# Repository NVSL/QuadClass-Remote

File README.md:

# CSE176e Quad Remote

## Assembly

## Parts

All the parts are on the course unified BOM: https://docs.google.com/spreadsheets/d/1jt7lCU-Biuc4YyG8EaISPEg1VLbqKCh2ZZRz8jerXEI/edit?gid=0#gid=0

## Laser Cutting

The plywood base and the "donuts" used for standoffs are all in the
`.brd` file.  Open it, hide everything but the `baseplate` layer.
Print it to a PDF and feed it to your laser cutter.

The wooden parts are cut from 3mm plywood (see parts list).

## The Gimbals

The gimbals attach to the baseplate with the 8 long machine screws and 8 nuts.  

## Board

The control board mounts to the baseplate using the shorter screws and nuts.  Use 3 donuts to put space between the board and the baseplate.

## Battery Cable

Red is positive.

Attach the battery and tuck it under the board.  You can trim the battery cable, if you want.  Experiment with different lengths.

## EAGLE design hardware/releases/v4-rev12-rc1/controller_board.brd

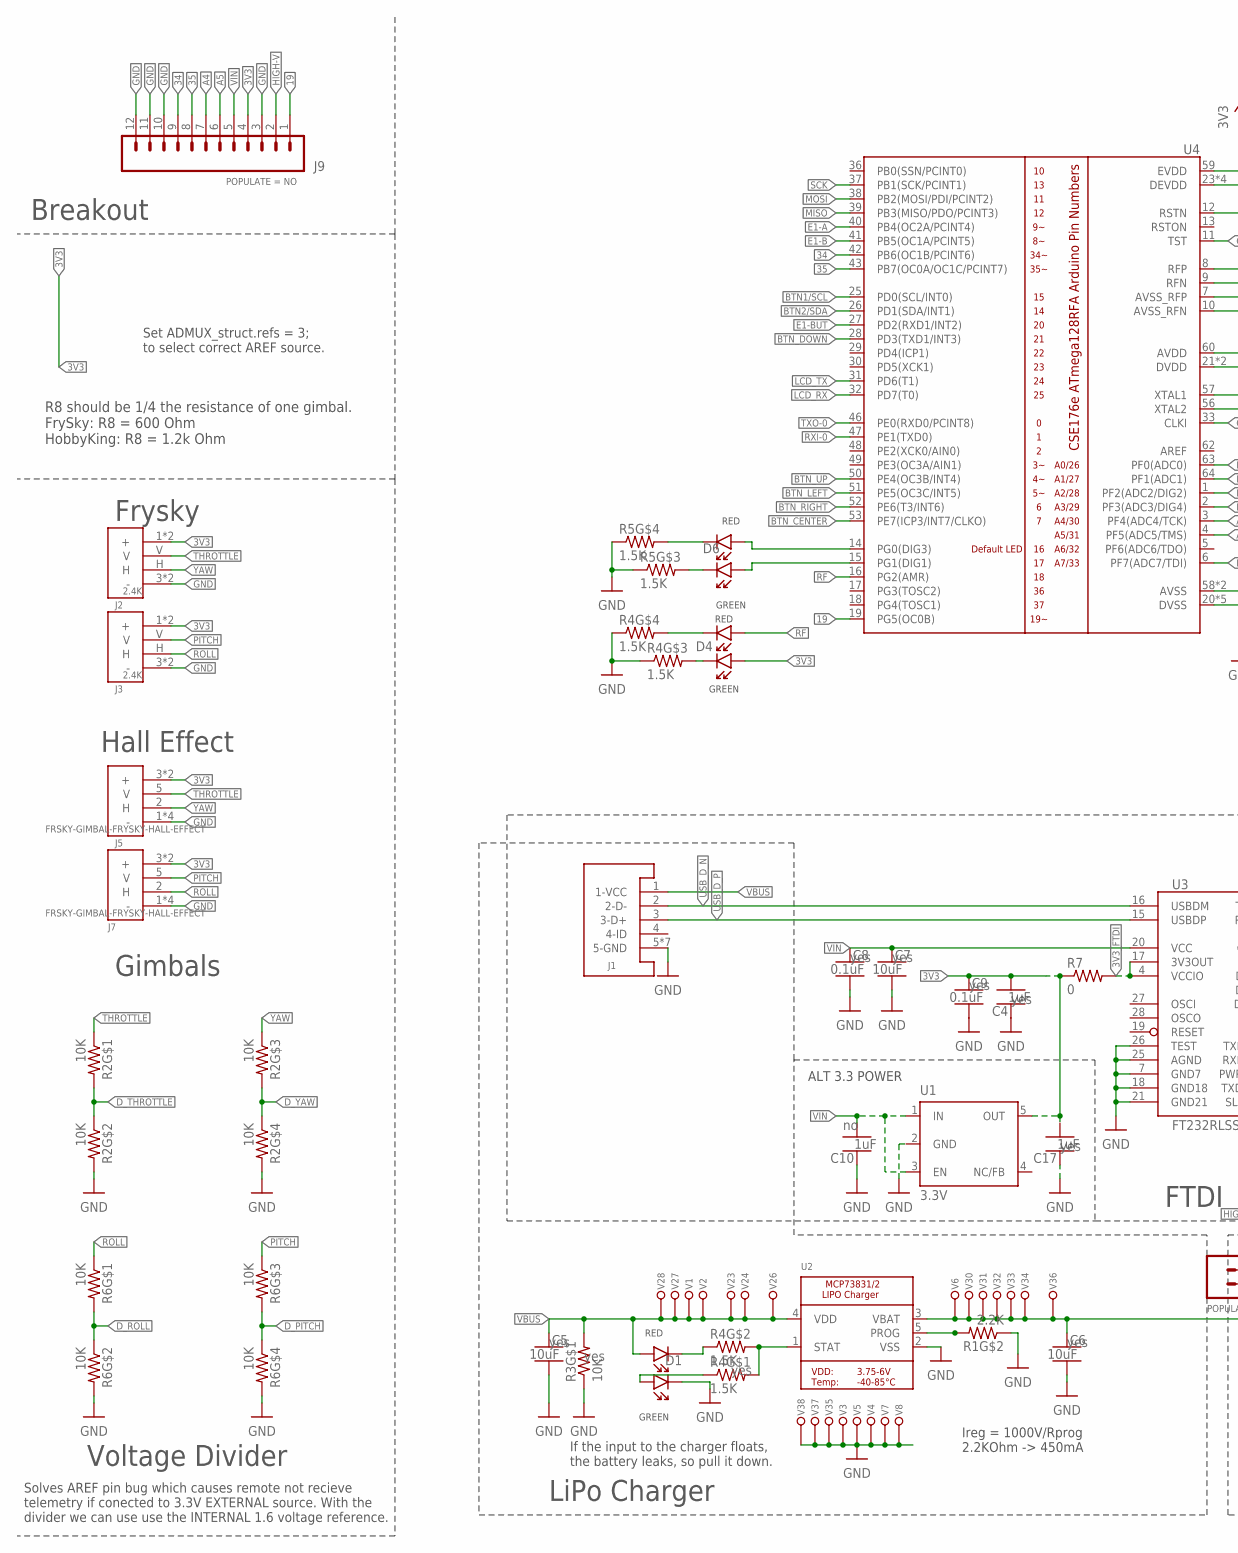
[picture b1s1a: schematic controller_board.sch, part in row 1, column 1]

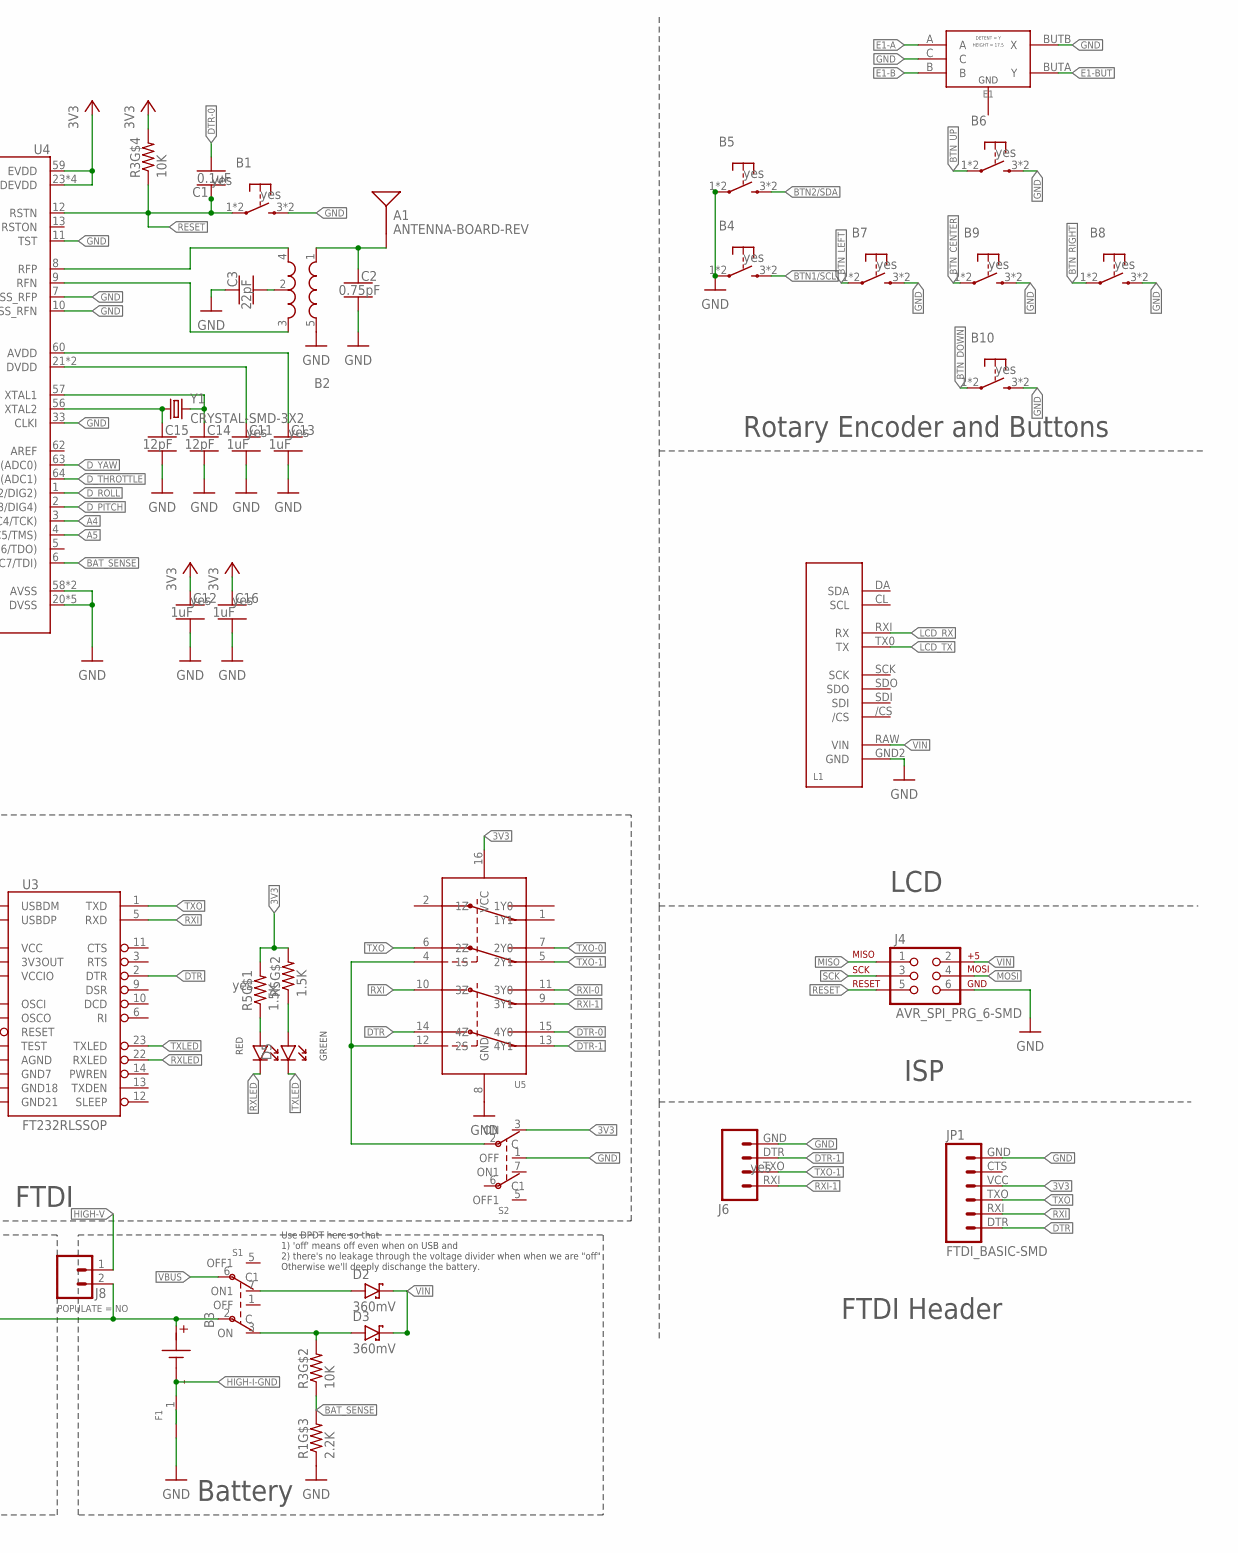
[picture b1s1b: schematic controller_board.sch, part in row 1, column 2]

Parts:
A1: ANTENNA-BOARD-REV; ANT_PCB_2.4GHZ_NRF8001_1.6MM_1OZ_REV
B1, B4, B5, B6, B7, B8, B9, B10: PUSHBUTTON_-4.5X4.5; 4.5MM_TACTILE_SWITCH_TL3305AF160QG
B2: BALUN0805; BALUN
B3: BATTERY-SCREW-TERMINAL; SCREW-TERMINAL-1X2-2.54MM
C1, C8, C9: 0.1uF; CAPC1608X100
C2: 0.75pF; CAPC1608X100
C3: 22pF; CAPC1608X100
C4, C10, C11, C12, C13, C16, C17: 1uF; CAPC1608X100
C5, C6, C7: 10uF; CAPC1608X100
C14, C15: 12pF; CAPC1608X100
D1, D4, D5, D6: LED-2X-GREEN/RED-1.6X1.5MM; LED-2X-LITE-ON-1.6MMX1.5MM
D2, D3: 360mV; SODFL3516X96
E1: ROTARY-ENCODER-W/BUTTON-BOURNS-PEC12R-4217F; BOURNS-PEC12R
F1: SHORT
J1: USB-MICROA-AMPHENOL-10118192-0001LF; USB-MICROA-10118192-0001LF
J2, J3: 2.4K; JST-13-PTH
J4: AVR_SPI_PRG_6-SMD; 2X3-SMD
J5, J7: FRSKY-GIMBAL-FRYSKY-HALL-EFFECT; MOLEX-0532610671
J6: FTDI-4PIN-RIGHT-ANGLE-SMD; HEADER-2X2-0.1IN-MALE-RIGHT-ANGLE-SMD
J8: HEADER-0.1IN-2POS-SCREW; SCREW-TERMINAL-1X2-2.54MM
J9: HEADER-12POS-0.1IN-FEMALE-TH; HDRVR12W75P254_1X12_3098X254X850B
JP1: FTDI_BASIC-SMD; FTDI-BASIC-SMD
L1: SPARKFUN_SERLCD_SERIAL_REDUCED-SMD; SPARKFUN_SERLCD_16X2_REDUCED_SMD
R1: 2.2K; RESCAXS50P200X100X45-8
R2, R3, R6: 10K; RESCAXS50P200X100X45-8
R4, R5: 1.5K; RESCAXS50P200X100X45-8
R7: 0; RESC1608X55
S1, S2: SWITCH-DPDT-300MA-6V-SMD; JS202011JCQN
U1: 3.3V; SOT23-DBV
U2: MCP73831T-2ACI/OT; SOT23-5
U3: FT232RLSSOP; SSOP28DB
U4: ATMEGA128RFA1; QFN-64
U5: DPDT-X2; SOP65P640X110-16
V1, V2, V3, V4, V5, V6, V7, V8, V23, V24, V26, V27, V28, V30, V31, V32, V33, V34, V35, V36, V37, V38: LOCKED-VIA-0.2; VIA-0.2MM
Y1: CRYSTAL-SMD-3X2; OSCCC320X250X85

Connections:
3V3: C4.2, C9.1, C12.1, C16.1, C17.2, D4.A1, J2.1 (+), J2.4 (+), J3.1 (+), J3.4 (+), J5.3 (+), J5.6 (+), J7.3 (+), J7.6 (+), J9.4, JP1.VCC (4), R3.8 (2), R5.5 (2), R5.6 (2), R7.1, S2.3 (ON), U1.5 (OUT), U4.23 (DEVDD), U4.34 (DEVDD), U4.44 (DEVDD), U4.54 (DEVDD), U4.59 (EVDD), U5.16 (VCC)
3V3_FTDI: R7.2, U3.4 (VCCIO), U3.17 (3V3OUT)
19: J9.1, U4.19 (PG5(OC0B))
34: J9.9, U4.42 (PB6(OC1B/PCINT6))
35: J9.8, U4.43 (PB7(OC0A/OC1C/PCINT7))
A4: J9.7, U4.3 (PF4(ADC4/TCK))
A5: J9.6, U4.4 (PF5(ADC5/TMS))
ANTENNA: A1.FEED, B2.1 (IN), C2.1
BAT_SENSE: R1.7 (2), R3.3 (1), U4.6 (PF7(ADC7/TDI))
BCAP: B2.2 (GND), C3.2
BPOS: B3.2, C6.1, J8.2 (1), S1.2 (C), U2.3 (VBAT), V6.P1, V30.P1, V31.P1, V32.P1, V33.P1, V34.P1, V36.P1
BTN1/SCL: B4.3 (2), B4.4 (2), U4.25 (PD0(SCL/INT0))
BTN2/SDA: B5.3 (2), B5.4 (2), U4.26 (PD1(SDA/INT1))
BTN_CENTER: B9.1, B9.2 (1), U4.53 (PE7(ICP3/INT7/CLKO))
BTN_DOWN: B10.1, B10.2 (1), U4.28 (PD3(TXD1/INT3))
BTN_LEFT: B7.1, B7.2 (1), U4.51 (PE5(OC3C/INT5))
BTN_RIGHT: B8.1, B8.2 (1), U4.52 (PE6(T3/INT6))
BTN_UP: B6.1, B6.2 (1), U4.50 (PE4(OC3B/INT4))
CLK_NEG: C15.1, U4.56 (XTAL2), Y1.1
CLK_POS: C14.1, U4.57 (XTAL1), Y1.3 (2)
DTR: JP1.DTR (1), U3.2 (DTR), U5.14 (4Z)
DTR-0: C1.2, U5.15 (4Y0)
DTR-1: J6.DTR (3), U5.13 (4Y1)
D_PITCH: R6.1, R6.7 (2), U4.2 (PF3(ADC3/DIG4))
D_ROLL: R6.3 (1), R6.5 (2), U4.1 (PF2(ADC2/DIG2))
D_THROTTLE: R2.3 (1), R2.5 (2), U4.64 (PF1(ADC1))
D_YAW: R2.1, R2.7 (2), U4.63 (PF0(ADC0))
E1-A: E1.A, U4.40 (PB4(OC2A/PCINT4))
E1-B: E1.B, U4.41 (PB5(OC1A/PCINT5))
E1-BUT: E1.BUTA (Y), U4.27 (PD2(RXD1/INT2))
GND: B1.3 (2), B1.4 (2), B2.5 (GND), B4.1, B4.2 (1), B5.1, B5.2 (1), B6.3 (2), B6.4 (2), B7.3 (2), B7.4 (2), B8.3 (2), B8.4 (2), B9.3 (2), B9.4 (2), B10.3 (2), B10.4 (2), C2.2, C3.1, C4.1, C5.2, C6.2, C7.2, C8.2, C9.2, C10.1, C11.2, C12.2, C13.2, C14.2, C15.2, C16.2, C17.1, D1.C1, E1.BUTB (X), E1.C, F1.2 (B), J1.5 (5-GND), J1.6 (5-GND), J1.7 (5-GND), J1.8 (5-GND), J1.9 (5-GND), J1.10 (5-GND), J1.11 (5-GND), J2.3 (-), J2.6 (-), J3.3 (-), J3.6 (-), J4.6, J5.1 (-), J5.4 (-), J5.G1 (-), J5.G2 (-), J6.GND (4), J7.1 (-), J7.4 (-), J7.G1 (-), J7.G2 (-), J9.3, J9.10, J9.11, J9.12, JP1.GND (6), L1.GND2 (GND), R1.2 (1), R1.3 (1), R2.6 (2), R2.8 (2), R3.4 (1), R4.1, R4.2 (1), R5.1, R5.2 (1), R6.6 (2), R6.8 (2), S2.1 (OFF), U1.2 (GND), U2.2 (VSS), U3.7 (GND7), U3.18 (GND18), U3.21 (GND21), U3.25 (AGND), U3.26 (TEST), U4.7 (AVSS_RFP), U4.10 (AVSS_RFN), U4.11 (TST), U4.20 (DVSS), U4.24 (DVSS), U4.33 (CLKI), U4.35 (DVSS), U4.45 (DVSS), U4.55 (DVSS), U4.58 (AVSS), U4.61 (AVSS), U5.8 (GND), V3.P1, V4.P1, V5.P1, V7.P1, V8.P1, V35.P1, V37.P1, V38.P1
HIGH-I-GND: B3.1 (N), F1.1 (A)
HIGH-V: J8.1 (2), J9.2
LCD_RX: L1.RXI (RX), U4.32 (PD7(T0))
LCD_TX: L1.TX0 (TX), U4.31 (PD6(T1))
MISO: J4.1, U4.39 (PB3(MISO/PDO/PCINT3))
MOSI: J4.4, U4.38 (PB2(MOSI/PDI/PCINT2))
unnamed: D1.A1, R4.4 (1)
unnamed: D1.C2, R4.3 (1)
unnamed: D5.A1, R5.3 (1)
unnamed: D6.C2, R5.8 (2)
unnamed: D6.C1, R5.7 (2)
unnamed: D4.C1, R4.7 (2)
unnamed: D5.A2, R5.4 (1)
unnamed: D6.A2, U4.14 (PG0(DIG3))
unnamed: D6.A1, U4.15 (PG1(DIG1))
unnamed: R4.5 (2), R4.6 (2), U2.1 (STAT)
unnamed: R1.6 (2), U2.5 (PROG)
unnamed: D4.C2, R4.8 (2)
unnamed: D2.2 (A), S1.7 (ON1)
unnamed: C11.1, U4.21 (DVDD), U4.22 (DVDD)
unnamed: C13.1, U4.60 (AVDD)
PITCH: J3.V, J7.5 (V), R6.2 (1)
PROG_SEL: S2.2 (C), U5.4 (1S), U5.12 (2S)
RESET: B1.1, B1.2 (1), C1.1, J4.5, R3.1, U4.12 (RSTN)
RF: D4.A2, U4.16 (PG2(AMR))
RF_N: B2.3 (OUT2), U4.9 (RFN)
RF_P: B2.4 (OUT1), U4.8 (RFP)
ROLL: J3.H, J7.2 (H), R6.4 (1)
RXI: JP1.RXI (2), U3.5 (RXD), U5.10 (3Z)
RXI-0: U4.47 (PE1(TXD0)), U5.11 (3Y0)
RXI-1: J6.RXI (1), U5.9 (3Y1)
RXLED: D5.C2, U3.22 (RXLED)
SCK: J4.3, U4.37 (PB1(SCK/PCINT1))
THROTTLE: J2.V, J5.5 (V), R2.4 (1)
TXLED: D5.C1, U3.23 (TXLED)
TXO: JP1.TXO (3), U3.1 (TXD), U5.6 (2Z)
TXO-0: U4.46 (PE0(RXD0/PCINT8)), U5.7 (2Y0)
TXO-1: J6.TXO (2), U5.5 (2Y1)
USB_D_N: J1.2 (2-D-), U3.16 (USBDM)
USB_D_P: J1.3 (3-D+), U3.15 (USBDP)
VBAT: D3.2 (A), R3.6 (2), S1.3 (ON)
VBUS: C5.1, D1.A2, J1.1 (1-VCC), R3.5 (2), S1.6 (C1), U2.4 (VDD), V1.P1, V2.P1, V23.P1, V24.P1, V26.P1, V27.P1, V28.P1
VIN: C7.1, C8.1, C10.2, D2.1 (C), D3.1 (C), J4.2, J9.5, L1.RAW (VIN), U1.1 (IN), U1.3 (EN), U3.20 (VCC)
YAW: J2.H, J5.2 (H), R2.2 (1)

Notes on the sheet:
Ireg = 1000V/Rprog 2.2KOhm -> 450mA
LiPo Charger
Breakout
Frysky
Hall Effect
Rotary Encoder and Buttons
Battery
LCD
ISP
FTDI Header
Set ADMUX_struct.refs = 3; to select correct AREF source.
Gimbals
R8 should be 1/4 the resistance of one gimbal. FrySky: R8 = 600 Ohm HobbyKing: R8 = 1.2k Ohm
If the input to the charger floats, the battery leaks, so pull it down.
FTDI
Use DPDT here so that 1) 'off' means off even when on USB and 2) there's no leakage through the voltage divider when when we are "off" Otherwise we'll deeply dischange the battery.
Voltage Divider
Solves AREF pin bug which causes remote not recieve telemetry if conected to 3.3V EXTERNAL source. With the divider we can use use the INTERNAL 1.6 voltage reference.
ALT 3.3 POWER

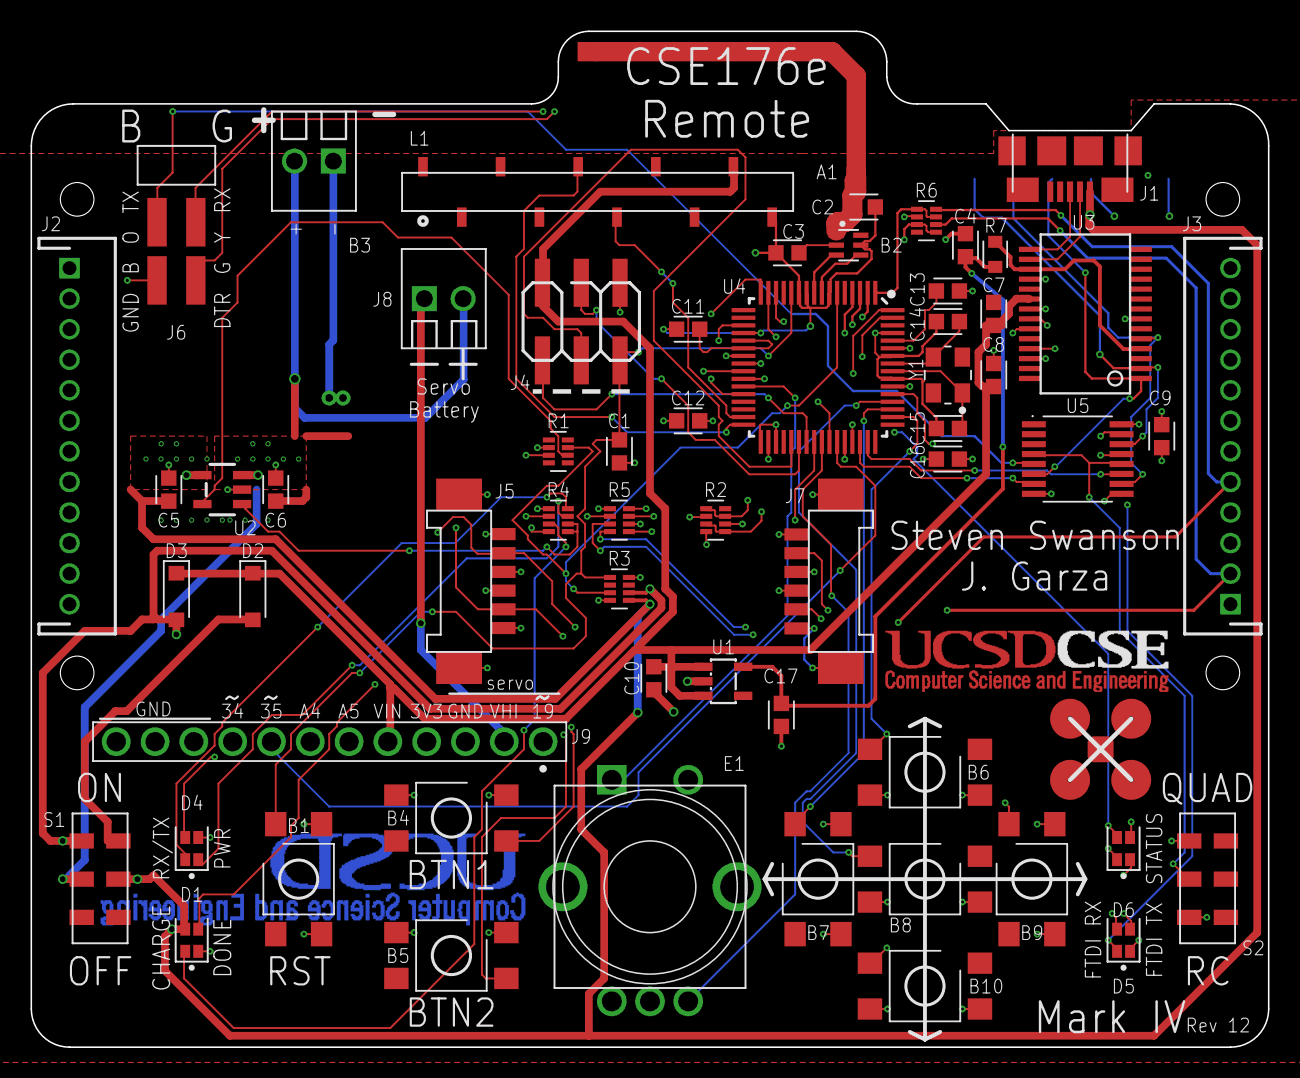
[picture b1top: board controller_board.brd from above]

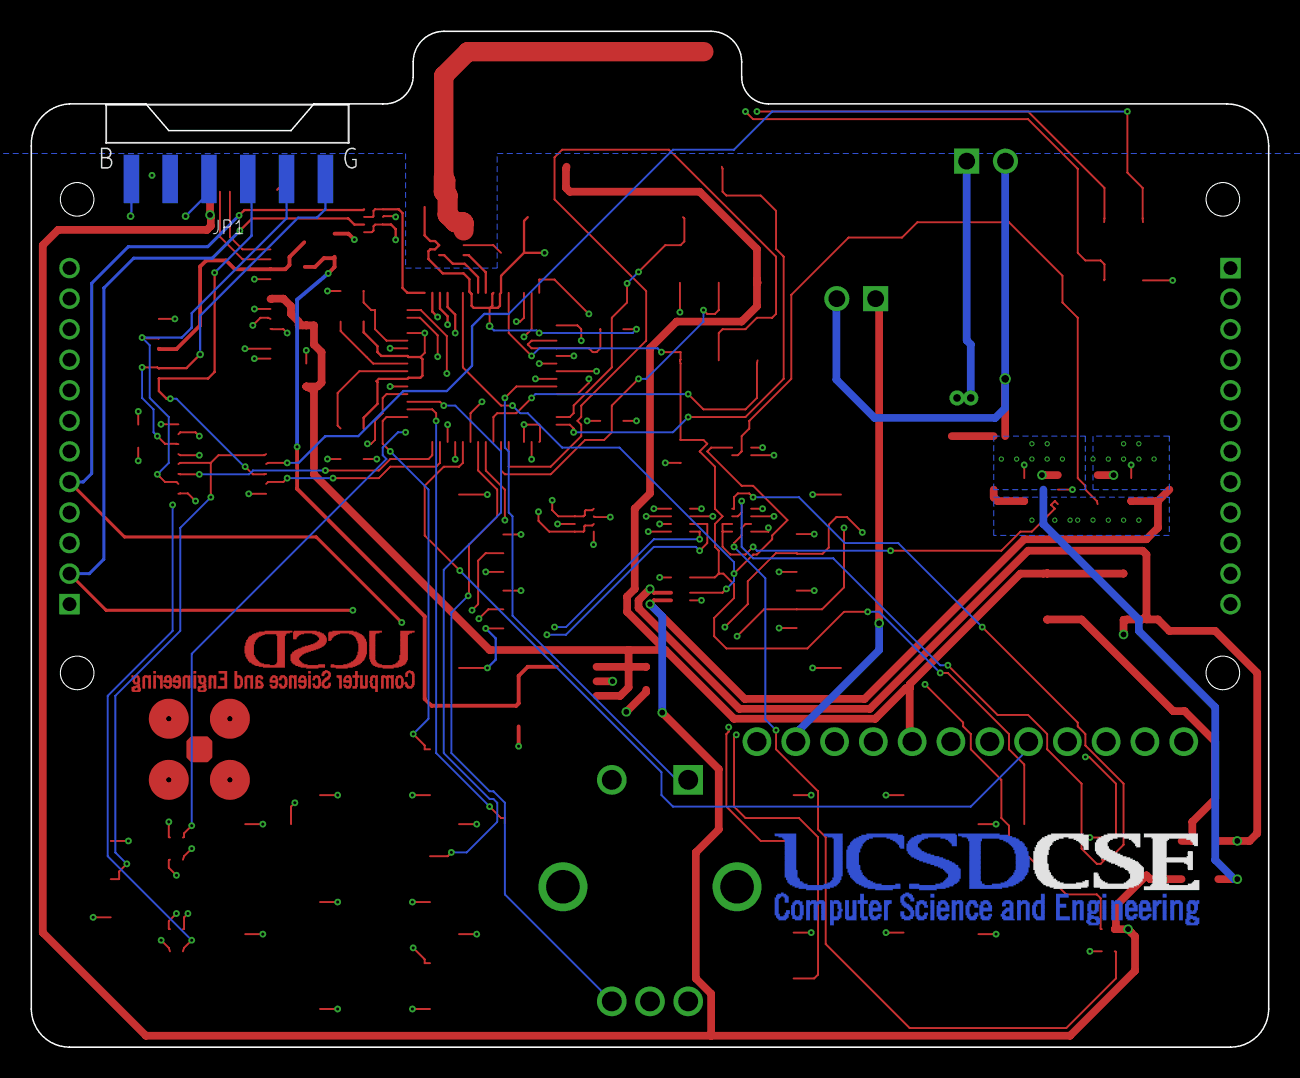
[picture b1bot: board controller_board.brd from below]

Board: 4 copper layers, 81.0 x 66.5 mm, 93 parts (2 on the bottom side), 75 nets.

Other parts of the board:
E$1, E$2: FRSKY-TARANIS-GIMBAL
U$1: 700MAH-BATTERY
U$2: QUADCLASS_LOGO_SMALL
U$3: LAYER_LABELS
U$4: 375MAH-BATTERY
U$5: 600MAH-BATTERY
U$6, U$7: CSE

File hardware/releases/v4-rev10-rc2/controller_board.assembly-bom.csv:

mfr,mfrpn,dist,distpn,part_list,qty,desc,value,substitute_ok,case,mounting,layer,pins,extended_pins,comments
C&K,JS202011JCQN,DIGIKEY,CKN10723CT-ND,S2 S1,2,SWITCH SLIDE DPDT 300MA 6V,SWITCH-DPDT-300MA-6V-SMD,no,,SMD,top,6,12,
Microchip Technology,ATMEGA128RFA1-ZU,DIGIKEY,ATMEGA128RFA1-ZU-ND ,U4,1,IC RF TXRX+MCU 802.15.4 64VFQFN,ATMEGA128RFA1,no,QFN,SMD,top,64,64,
Samsung Electro-Mechanics,CL10A105KP8NNNC,DIGIKEY,1276-1182-1-ND,C4 C13 C12 C11 C16,5,CAP CER 1UF 10V X5R 0603,1uF,yes,0603,SMD,top,2,10,
Abracon LLC,ABM8-16.000MHZ-B2-T,DIGIKEY,535-9134-1-ND,Y1,1,CRYSTAL 16.0000MHZ 18PF SMD,CRYSTAL-SMD-3X2,no,,SMD,top,4,4,
UNKNOWN,UNKNOWN,ALIBABA,https://www.alibaba.com/product-detail/Molex-51005-51006-2-p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,B3,1,Surface mount  battery connector,BATTERY-SMD,no,,SMD,top,4,4,
Sullins Connector Solutions,NPPC101KFXC-RC,DIGIKEY,S5641-ND,L1,1,"10 Position Header, Top or Bottom Entry Connector  Surface Mount",SPARKFUN_SERLCD_SERIAL_REDUCED-SMD,no,,SMD,top,10,10,
Toshiba Semiconductor and Storage,"CRS08(TE85L,Q,M)",DIGIKEY,CRS08QMCT-ND,D2 D3,2,DIODE SCHOTTKY 30V 1.5A SFLAT,360mV,no,,SMD,top,2,4,
Yageo,CC0603BRNPO9BNR75,DIGIKEY,311-3843-1-ND,C2,1,CAP CER 0.75PF 50V NPO 0603,0.75pF,no,0603,SMD,top,2,2,
Amphenol ICC (FCI),95278-101A06LF,DIGIKEY,609-3487-2-ND,J4,1,CONN HEADER SMD 6POS 2.54MM,AVR_SPI_PRG_6-SMD,no,,SMD,top,6,6,
Bourns Inc.,PEC12R-4217F-S0024,DIGIKEY,PEC12R-4220F-S0024-ND,E1,1,ROTARY ENCODER MECHANICAL 24PPR,ROTARY-ENCODER-W/BUTTON-BOURNS-PEC12R-4217F,NO,,TH,top,7,7,
Microchip Technology,MCP73831T-2ACI/OT,DIGIKEY,MCP73831T-2ACI/OTCT-ND,U2,1,IC CONTROLLR LI-ION 4.2V SOT23-5,MCP73831/2,no,SOT23-5,SMD,top,5,5,
AVX Corporation,06036A220KAT2A,DIGIKEY,478-11384-1-ND,C3,1,CAP CER 22PF 6.3V NP0 0603,22pF,no,0603,SMD,top,2,2,
Panasonic Electronic Components,EXB-N8V103JX,DIGIKEY,Y10103CT-ND,R3,1,RES ARRAY 4 RES 10K OHM 0804,10K,yes,0804,SMD,top,8,8,
Lite-On Inc.,LTST-C195TGKRKT,DIGIKEY,160-2252-1-ND,D6 D4 D5 D1,4,LED GREEN/RED CLEAR CHIP SMD,LED-2X-GREEN/RED-1.6X1.5MM,no,4SMD,SMD,top,4,16,
KEMET,C0603C104K8RACTU,DIGIKEY,399-1095-1-ND,C9 C8 C1,3,CAP CER 0.1UF 10V X7R 0603,0.1uF,yes,0603,SMD,top,2,6,
Amphenol ICC (FCI),10118192-0001LF,DIGIKEY,609-4613-1-ND ,J1,1,CONN RCPT USB2.0 MICRO B SMD R/A,USB-MICROA-AMPHENOL-10118192-0001LF,no,,SMD,top,11,11,
E-Switch,TL3305AF160QG,DIGIKEY,EG5350CT-ND,B4 B5 B6 B7 B1 B8 B9 B10,8,SWITCH TACTILE SPST-NO 50MA 12V,PUSHBUTTON_-4.5X4.5,yes,,SMD,top,4,32,
Samtec Inc.,TSM-102-01-L-DH,DIGIKEY,SAM15344-ND,J6,1,CONN HEADER SMD R/A 4POS 2.54MM,FTDI-4PIN-RIGHT-ANGLE-SMD,yes,,SMD,top,4,4,
FTDI,FT232RL-REEL,DIGIKEY,768-1007-1-ND ,U3,1,IC USB FS SERIAL UART 28-SSOP,FT232RLSSOP,no,,SMD,top,28,28,
Panasonic Electronic Components,EXB-N8V222JX,DIGIKEY,Y10222CT-ND,R1,1,RES ARRAY 4 RES 2.2K OHM 0804,2.2K,yes,,SMD,top,8,8,
Panasonic Electronic Components,EXB-N8V152JX,DIGIKEY,Y10152CT-ND,R4 R5,2,RES ARRAY 4 RES 1.5K OHM 0804,1.5K,yes,,SMD,top,8,16,
Samsung Electro-Mechanics,CL10A106MQ8NNNC,DIGIKEY,1276-1119-1-ND,C7 C6 C5,3,CAP CER 10UF 6.3V X5R 0603,10uF,yes,0603,SMD,top,2,6,
NXP USA Inc.,"NX3L2467PW,118",DIGIKEY,568-5300-1-ND,U5,1,IC ANALOG SWITCH DPDT 16TSSOP,DPDT-X2,no,,SMD,top,16,16,
Molex,0532610671,DIGIKEY,WM7624CT-ND,J5 J7,2,CONN HEADER SMD R/A 6POS 1.25MM,FRSKY-GIMBAL-FRYSKY-HALL-EFFECT,no,,SMD,top,8,16,
Vishay Vitramon,VJ0603A120FXQCW1BC,DIGIKEY,720-1655-1-ND,C15 C14,2,CAP CER 12PF 10V C0G/NP0 0603,12pF,no,0603,SMD,top,2,4,
Wurth Electronics Inc.,748421245,DIGIKEY,732-2230-1-ND,B2,1,BALUN 2.4GHZ-2.5GHZ 50/100 0805,BALUN0805,no,0805,SMD,top,6,6,

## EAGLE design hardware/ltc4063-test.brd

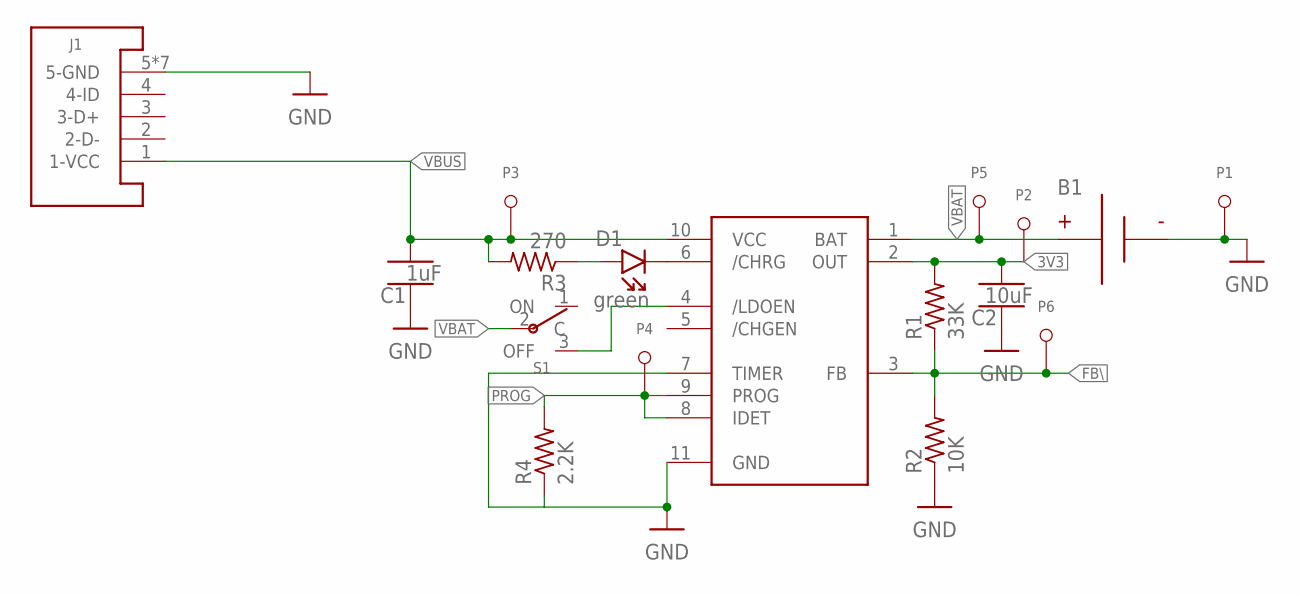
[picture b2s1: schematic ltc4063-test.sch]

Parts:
B1: BATTERY-SPRING-SMD; WIRE-TERMINAL-1X2-2.5MM-SMD-AVX-009276002021106
C1: 1uF; CAPC2012X140_HS
C2: 10uF; CAPC2012X140_HS
D1: green; LEDSC125X200X120-2_HS
J1: USB-MICROA-AMPHENOL-10118192-0001LF; USB-MICROA-10118192-0001LF
P1, P2, P3, P4, P5, P6: TEST-POINT; TEST-POINT-KEYSTONE-5000
R1: 33K; RESC2012X60_HS
R2: 10K; RESC2012X60_HS
R3: 270; RESC2012X60_HS
R4: 2.2K; RESC2012X60_HS
S1: POWER-SWITCH-MFS201N-9-Z-SMD-VERTICAL; JS102011JCQN
U1: LIPO-VREG-LTC4063; SON50P300X300X80-11T165X238

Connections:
3V3: C2.2, P2.T, R1.2, U1.2 (OUT)
FB\: P6.T, R1.1, R2.2, U1.3 (FB)
GND: B1.2A (N), B1.2B (N), C1.1, C2.1, J1.5 (5-GND), J1.6 (5-GND), J1.7 (5-GND), J1.8 (5-GND), J1.9 (5-GND), J1.10 (5-GND), J1.11 (5-GND), P1.T, R2.1, R4.1, U1.7 (TIMER), U1.11 (GND)
unnamed: S1.3 (OFF), U1.4 (/LDOEN)
unnamed: D1.C, U1.6 (/CHRG)
unnamed: D1.A, R3.1
PROG: P4.T, R4.2, U1.8 (IDET), U1.9 (PROG)
VBAT: B1.1A, B1.1B, P5.T, S1.2 (C), U1.1 (BAT)
VBUS: C1.2, J1.1 (1-VCC), P3.T, R3.2, U1.10 (VCC)

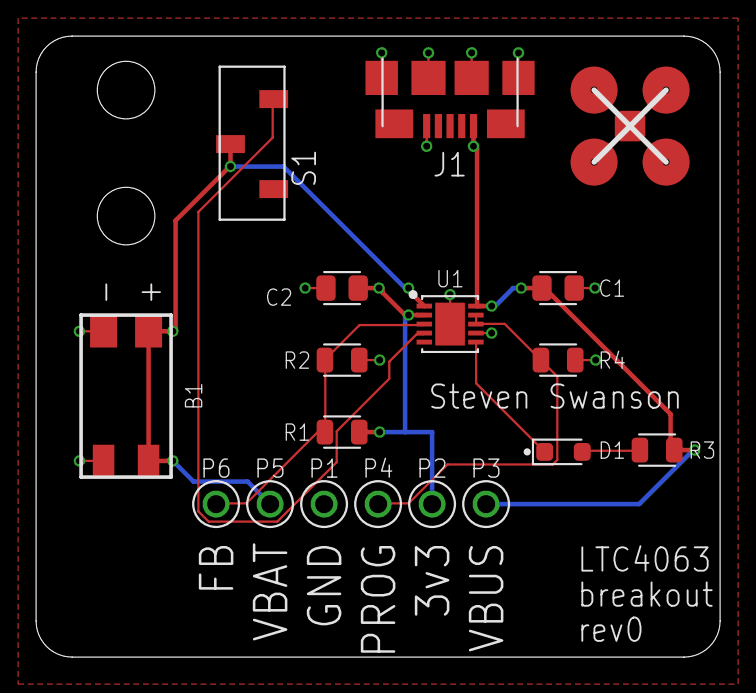
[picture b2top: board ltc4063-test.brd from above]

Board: 2 copper layers, 38.0 x 34.5 mm, 18 parts (0 on the bottom side), 9 nets.

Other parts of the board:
U$1: QUADCLASS_LOGO_SMALL

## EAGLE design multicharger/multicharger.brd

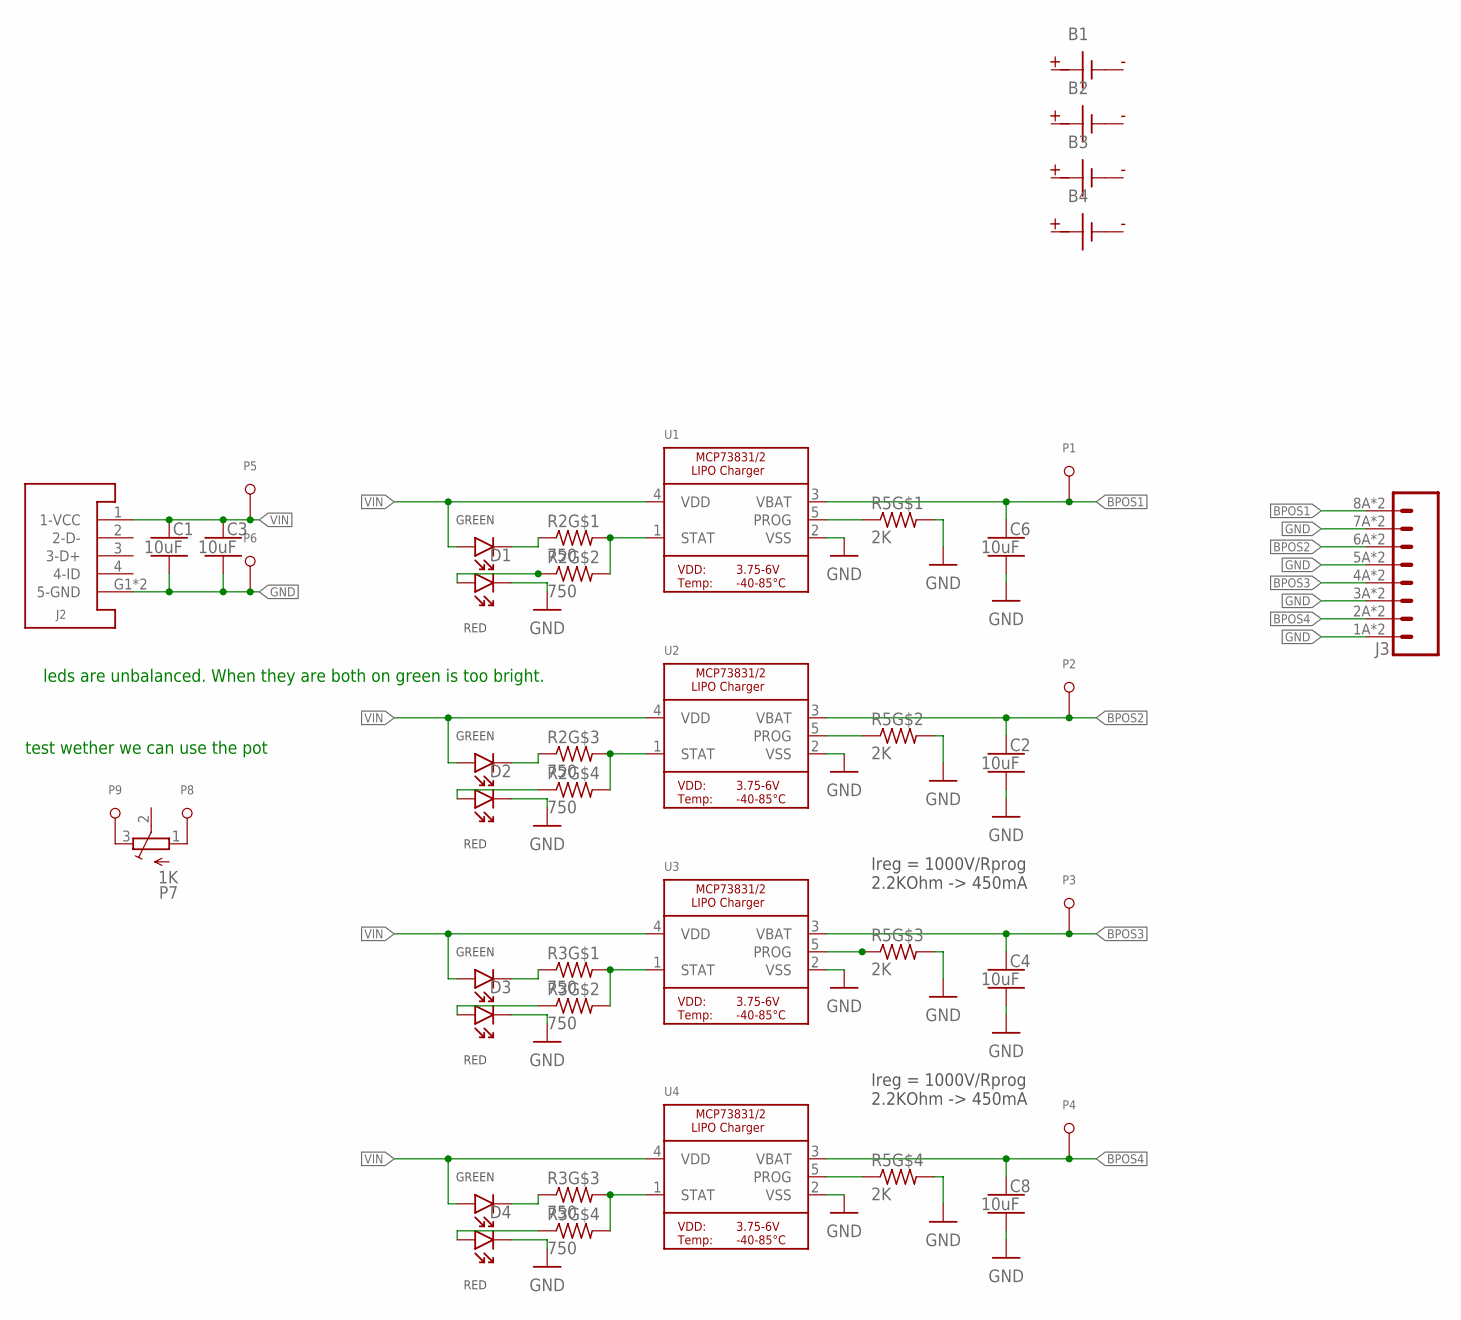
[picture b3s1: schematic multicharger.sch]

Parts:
B1, B2, B3, B4: BATTERY-SMD; MOLEX-BATTERY-CONNECTOR-SMD-51005-2P
C1, C2, C3, C4, C6, C8: 10uF; CAPC1608X100
D1, D2, D3, D4: LED-2X-GREEN/RED-1.6X1.5MM; LED-2X-LITE-ON-1.6MMX1.5MM
J2: USB-A-SMD-KEYSTONE-931; USB-A-KEYSTONE-931
J3: HEADER-8POS-; WIRE-TERMINAL-1X8-2.5MM-SMD
P1, P2, P3, P4, P5, P6, P8, P9: TEST-POINT-1MM; TEST-POINT-1MM-VIA
P7: 1K; BOT-ADJUST-POT-3314R-1-103E
R2, R3: 750; RESCAXS50P200X100X45-8
R5: 2K; RESCAXS50P200X100X45-8
U1, U2, U3, U4: MCP73831T-2ACI/OT; SOT23-5

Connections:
BPOS1: C6.1, J3.8A (8), J3.8B (8), P1.T, U1.3 (VBAT)
BPOS2: C2.1, J3.6A (6), J3.6B (6), P2.T, U2.3 (VBAT)
BPOS3: C4.1, J3.4A (4), J3.4B (4), P3.T, U3.3 (VBAT)
BPOS4: C8.1, J3.2A (2), J3.2B (2), P4.T, U4.3 (VBAT)
GND: C1.2, C2.2, C3.2, C4.2, C6.2, C8.2, D1.C1, D2.C1, D3.C1, D4.C1, J2.G1 (5-GND), J2.G2 (5-GND), J3.1A (1), J3.1B (1), J3.3A (3), J3.3B (3), J3.5A (5), J3.5B (5), J3.7A (7), J3.7B (7), P6.T, R5.5 (2), R5.6 (2), R5.7 (2), R5.8 (2), U1.2 (VSS), U2.2 (VSS), U3.2 (VSS), U4.2 (VSS)
unnamed: D1.A1, R2.3 (1)
unnamed: D1.C2, R2.4 (1)
unnamed: R2.7 (2), R2.8 (2), U2.1 (STAT)
unnamed: R5.3 (1), U2.5 (PROG)
unnamed: D2.A1, R2.1
unnamed: D2.C2, R2.2 (1)
unnamed: R3.5 (2), R3.6 (2), U3.1 (STAT)
unnamed: R5.2 (1), U3.5 (PROG)
unnamed: D3.A1, R3.3 (1)
unnamed: D3.C2, R3.4 (1)
unnamed: R2.5 (2), R2.6 (2), U1.1 (STAT)
unnamed: R5.4 (1), U1.5 (PROG)
unnamed: R3.7 (2), R3.8 (2), U4.1 (STAT)
unnamed: R5.1, U4.5 (PROG)
unnamed: D4.A1, R3.1
unnamed: D4.C2, R3.2 (1)
unnamed: P7.1 (A), P8.T
unnamed: P7.3 (E), P9.T
VIN: C1.1, C3.1, D1.A2, D2.A2, D3.A2, D4.A2, J2.1 (1-VCC), P5.T, U1.4 (VDD), U2.4 (VDD), U3.4 (VDD), U4.4 (VDD)

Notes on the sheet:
Ireg = 1000V/Rprog 2.2KOhm -> 450mA
leds are unbalanced. When they are both on green is too bright.
test wether we can use the pot

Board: 4 copper layers, 33 parts (7 on the bottom side), 24 nets, no tracks yet.

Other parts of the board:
U$2: QUADCLASS_LOGO

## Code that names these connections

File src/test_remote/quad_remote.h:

/* quad_remote.h
 * Provides pin defn's and setup for ATmega128RFA1.
 * Components:
 * 		Gimbal
 * 		Potentiometers (POT1 and POT2)
 * 		Buttons
 * 		Indicator LEDs
 */
#include <Arduino.h>

// Pin definitions for Gimbals (Analog inputs).  It is not clear why the A1, A2,... etc. don't work, but they don't.
#define PIN_YAW			0 //A0
#define PIN_THROTTLE 	1// A1 
#define PIN_ROLL		2// A2 
#define	PIN_PITCH		3//A3  

// Pin definitions for potentiometers (Analog inputs)
#define PIN_POT1		7//A7
#define PIN_POT2		6//A6

// Pin definitions for digital pins (buttons and indicator LEDs)
#define PIN_BTN1		16		// PG0 (schematic) G0 (red board)
#define PIN_BTN2		17		// PG1 (schematic) G1 (red board)
#define PIN_LED_BLUE	22		// PD6 (schematic) D4 (red board)
#define PIN_LED_GRN		23		// PD5 (schematic) D5 (red board)
#define PIN_LED_RED		24		// PD4 (schematic) D6 (red board)		

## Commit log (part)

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2017-03-19 Give the remote its own repo
2017-03-25 Move gimbals to the underside, move leds so they are so bright an annoying
2017-03-26 Refinement based on prototype
2017-03-31 test sketch and header for remote
2017-04-01 fix polarity on butons. Connect unconnected pin on batgnd breakouts
2017-04-01 remove support for old gimbals
2017-04-01 small tweak it logo position
2017-04-01 update comments
2017-04-01 SHow readings on lcd
2017-04-01 small changes
2017-04-03 reorg
2017-04-03 cleanup
2017-04-03 cleanup and use the radio library
2017-04-03 consolidate RemoteParts libraries
2017-04-03 gitignore and libs
2017-05-19 description of fix for receive problem
2018-03-10 new radio lib
2018-03-10 improved remote tester
2018-03-10 Testing harness code for testing a remote
2018-03-10 cleanup schematic
2018-03-10 import a bunch of components from quad schematic. remove arduino breakout
2018-03-10 cleanup and a few schematic fixes
2018-03-10 fix gnd issue on ISP header
2018-03-14 small fixes. going through check list
2018-03-15 taped out for jlcpcb
2018-03-15 Rev1-rc1 tape out for 4pcb
2018-03-15 Rev1-rc2 tape out for jlcpcb
2018-05-12 Removed dedicated ground plane for antenna; merged with L2 ground plane; added ground pour on top of the board. Moved FTDI programming header and mattery connector down.
    Updated silkscreen as Rev2.
    Updated test code to match new hardware
2018-05-12 Inclued radio receive in test along with new analog channels
2018-05-13 surface mount buttons and power led
2018-05-13 Surface mount power switch
2018-05-13 move power switch out of the way
2018-05-13 use 3.3V regulator
2018-05-13 smash and reorg most stuff. Add 10uF caps
2018-05-13 first draft of FTDI integration
2018-05-14 merged a bunch of parts into lbr. Laid everything out.
2018-05-14 First draft of power supply test board
2018-05-14 move pour under battery charger to bpos
2018-05-15 cleanup; small fixes; mosfet for power switching; disable charging on sleep
2018-05-15 design review and egalint
2018-05-15 power test board RC1
2018-05-16 I didn't add these before I committed RC1 and then I modified them, so they don't quite match what was ordered. Only difference around the pours/heatsink for the battery charger
2018-05-16 revert controller board
2018-05-17 grid settings
2018-05-23 smaller caps
2018-05-30 adjust resistor values after some testing. make GND an High-I net.
2018-05-30 Move pwren pull up to 3.3V rail in accordance with datasheet
2018-05-30 move C13 and FTDI to make it easier to solder on the FTDI.
2018-05-30 notes on power_test board and bringup
2018-05-31 notes about bringup
2018-05-31 fix red led polarity
2018-05-31 full breakout for battery charger. remove voltage regulator. Flip one FTDI port. New source switching scheme. Remove various jumpers. Fix Red LEDs
2018-06-05 verified 3.7V opertaion of ftdi regulator. checked circuit on bread board
2018-06-05 Initial layout of Mark 3 board and baseplate
2018-06-07 Layout complete for rc1
2018-06-07 Library of logos
2018-06-07 manual routing done for rc1
2018-06-07 clearer gerber labels. Some Bling\!
2018-06-07 remove bling...
2018-06-07 rc2 complete
2018-06-07 rc3 complete. Small tweaks
2018-06-08 sketch of board with LCD
2018-06-08 Sparkfun RGB backlight LCD
2018-06-11 vertical switch
2018-06-14 Significant redesign to accomodate LCD
2018-06-14 sketch of board with jog dial
2018-06-14 Fix stencil fiducial to fill in tcream hole
2018-06-17 Added rotary encoders, correctly wired LCD, reworked layout.
2018-06-18 small adjustments
2018-06-19 Adjust encoder height. Gimbal holes. Servo connector placement.
2018-06-19 fix gimbal wiring in device
2018-06-23 Cleanly support monochrome and RGB LCDs. Put all buttons and encoders on interrupts. New pin assignments. New uCtrl symbol
2018-06-23 new symbols for gimbals
2018-06-24 support cheaper version. Make the schematic pretty
2018-06-24 add separate 3.3v regulator
2018-06-24 add jumper to select vreg
2018-06-24 new test points
2018-06-25 Mark IV rev1, rc1
2018-06-25 Mark IV rev1, rc2
2018-06-25 Mark IV rev1, rc3
2018-06-26 small tweaks; final routing; rc4
2018-06-26 small tweaks; final routing; rc5
2018-06-26 small tweaks; clean up charger heat sink; rc6
2018-06-26 Silkscreen; rc7
2018-06-26 controller_board tapeout
2018-06-29 notes from undergrads. Tweak stencil fiducial. Some new parts
2018-07-04 All buttons, no encoders
2018-07-05 Reduced controls. Increased configurability. Defaults to minimal configuration
2018-07-06 notes from assembly; improved donuts
2018-07-07 fix a few small bugs -- rotate ISP programmer more space around board
2018-07-08 test harness for Mark IV rev 2
2018-07-09 reindent
2018-07-09 Complete test firmware for Mark IV rev2; Battery sensing, nice display + color control. Interrupt+callback interface.
2018-07-09 Remove option for 3v3 from FTDI. Cleanup; Edge-mounted switches.
2018-07-09 Bypass power switch. Rearrange circuit to share input cap on vreg and bat charger
2018-07-10 placed all reference designators and values
2018-07-10 small tweaks to increase symmetry
2018-07-10 simplify design
2018-07-10 added configuration jumpers for AREF
2018-07-10 silkscreen touch up
2018-07-11 moved everything to dual LEDs w/ shared resistors.
2018-07-11 note about using a bigger cap for the reset
2018-07-12 part for new encoder
2018-07-13 handrouting done
2018-07-13 Fully routed. Rc2
2018-07-14 define assembly variants
2018-07-27 added 'MOUNTING' attribute to all parts
2018-07-27 connect PWR led to power
2018-08-25 updated test and quadcopter lib code and a critical fix in radio.h rfRead()
2018-08-26 go back to one resistor-per-led
2018-08-26 Surface mount 6-pin header
2018-08-26 rearrange board and add holes in baseplate to make assembly easier
2018-08-26 imperial mounting holes
2018-08-26 update notes on stackup. Mark as rev4
2018-08-26 Notes about upgrading to FTDI
2018-08-26 use trace-connected jumpers. Put them on the back of the board
2018-08-27 renumber resistors
2018-08-27 renumber buttons, diodes, capacitors, ICs, test points
2018-08-27 hand routing done
2018-08-28 smaller holes. Sparkfun SERLCD added to library.
2018-08-28 obsevively align everything
2018-08-28 obsevively align everything; routed. RC1.
2018-08-28 Reduce BOM lines by reconfigure reset circuit
2018-08-28 obsevively align everything; routed. RC2.
2018-08-28 fix one net class.
2018-08-28 Fix DRC width errors. RC3.
2018-08-28 .gitignore
2018-08-28 Added IMU.
2018-08-29 Silkscreen adjust. RC5.
2018-08-29 update list of non-core components
2018-08-29 small adjustments. Rearrange controls
2018-08-30 Adjust silkscreen text. prerouting done.
2018-08-30 more hand-routing
2018-09-03 smaller pads for better routing
2018-09-03 RC6, fully routed
2018-09-06 fix incorrect resistor part number
2018-12-27 massive library cleanup
2018-12-27 Library cleanup
2018-12-29 updated error approvals
2018-12-29 logo and missing antenna
2018-12-29 Artwork errors
2019-01-01 metal layer labels
2019-02-14 Fix color of charger indicator LEDs
2019-02-15 software updates for Rev 4. Move FTDI over a bit to accomodate battery.
2019-02-16 sketch of assembly instructions
2019-02-16 silly artwork
2019-02-18 libs pass lint
2019-02-18 passes lint
2019-02-20 Update test target. Add IMU back
2019-02-21 fully routed.
2019-02-21 adjust version number
2019-02-25 Clean up table.
2019-02-25 scripts for generating partial boms for students
2019-02-26 rerouting script
2019-02-26 rename libraries
2019-02-26 library properties
2019-03-02 update libraries
2019-03-02 new release organization
2019-03-02 automate board package install
2019-03-02 Update code for v4-rev5. LCD not working.-a
2019-03-02 Update code for v4-rev5. LCD not working.
2019-03-04 factor out radio.cpp
2019-03-08 bump revision number. Run vbat through power switch
2019-03-08 change stripped down configuration to include FTDI in all cases and not include switch
2019-03-08 rename constants
2019-03-08 enable the LCD again, sort of. Communication is unidirectional, which causes flow control problems when you try to change the backlight
2019-03-22 enable ftdi by default. Make power switch non-optional
2019-03-22 Remove donuts
2019-04-07 add is_pressed() to example
2019-04-07 add securrentpos() to demo
2019-04-16 update demo apps
2019-04-17 vastly improved rotary encoder library
2019-04-17 update example and handle fractional updates more cleanly
2019-05-05 reorder pin names to match what we use in the firmware
2019-05-07 significant reorg to improve control layout and simplify design
2019-05-09 Reorg mostly complete. Mostly routed
2019-05-09 routed. double battery terminals
2019-05-09 fix makefile
2019-05-09 accept spurious errors
2019-05-09 cleanup makefile. Bump version
2019-05-10 update layout
2019-05-11 reorg. larger board. More spacious. Strain relief for the battery
2019-05-11 resolve meaningless merge
2019-05-14 baby steps toward routabilty
2019-05-15 All routed with shield gnd to control routing
2019-05-15 bump version. routed and decorated.
2019-05-15 Release v4-rev6-rc3
2019-05-15 restore shield
2019-05-15 Release v4-rev6-rc4
2019-05-16 passes eaglint.
2019-05-16 Release v4-rev6-rc6
2019-05-16 add vreg back. routed
2019-05-16 Release v4-rev6-rc7
2019-05-17 bump version. Remove screw terminal battery
2019-05-17 placed and routed w/vreg
2019-05-17 LTC4063 test board
2019-05-17 parts for LTC4063
2019-05-17 reformat xml
2019-05-17 tweak board shape
2019-05-18 Release v1-rev0-rc2
2019-05-19 bump revision
2019-05-20 4x lipo charger. Placed and routed.
2019-05-20 smaller LEDs for multi-charger
2019-05-20 make file, better-looking layout
2019-05-20 routed
2019-05-20 fix wierd attribute placement
2019-05-20 Release multicharger-v1-rev0-rc1
2019-05-21 cosmetic changes to schematic
2019-05-31 ADding missing files. Not sure where they went.
2019-05-31 adding missing files. Not sure where they went
2019-05-31 pretty, compact, USB-A version of multicharger
2019-05-31 Bigger resistors on leds
2019-06-10 tweaks to multi-charger
2019-06-14 reorg to more compacness
2019-06-18 0603. Fixed courtyards. chip antenna
2019-06-18 fix wierd bug.
2019-06-18 Release controller_board-v4-rev7-rc1
2019-06-21 More compact design
2019-06-21 Release controller_board-v4-rev7-rc2
2019-06-23 reroute.
2019-06-23 Release controller_board-v4-rev7-rc3
2019-06-23 reroute. pass quadlint.
2019-06-23 Release controller_board-v4-rev7-rc4
2019-06-23 Release controller_board-v4-rev7-rc5
2019-07-03 part way to 4-pin connectors
2019-07-05 cosmetic changes. use 4-pin ftdi
2019-07-07 cleanup. Avoid leakage on battery sense
2019-10-04 drc and eaglint clean
2019-10-04 mfr data for assembly house
2019-10-30 part updates
2020-02-04 rev 8
2020-02-12 final tweaks and routed
2020-02-12 metadat for assembly
2020-02-12 new relaese
2020-02-12 Release controller_board-v4-rev8-rc2
2020-02-13 new revision for fixed bom
2020-02-13 Release controller_board-v4-rev8-rc3
2020-02-13 turn off assembly bom
2020-02-13 Release multicharger-redux-v1-rev1-rc1
2020-03-17 who knows
2020-04-28 adjust placement of text
2020-05-01 silkscreen updates and restore missing GND test point
2020-08-31 new rev. to try to fix radio probleme
2020-08-31 move antenna
2020-08-31 trace antenna + pours + hand routing
2020-09-12 passes eaglint
2020-09-12 Release controller_board-v4-rev9-rc1
2020-11-20 bump rc for full manufacturing
2020-11-20 Release multicharger-redux-v1-rev1-rc2
2020-11-26 bump rc
2020-11-26 Release multicharger-redux-v1-rev1-rc3
2020-12-09 radio tuning
2020-12-09 Bump version. add missing gerbers for multicharger
2020-12-09 remove extraneous output
2021-02-20 rev 10, routed
2021-02-20 fix wire bridge
2021-02-21 fix attrs
2021-02-21 Release controller_board-v4-rev10-rc2
2021-02-21 add protrusion on the bottom of the LCD. better routing script
2021-02-21 use 1.6V reference
2021-02-26 Release controller_board-v4-rev10-rc4
2021-02-26 routing fixes
2021-02-26 Release controller_board-v4-rev10-rc5
2021-02-26 Release controller_board-v4-rev10-rc6
2021-12-31 unknown changes from long ago. And updating drill sizes for bigger screws
2023-01-20 Adding screw terminal block orientation
2023-01-20 Updated board with screw terminal orientation
2023-01-26 Removing AREF & Adding voltage divider for gimbals
2023-02-02 Remote gerber with ARF fix, Sent to fab Jan-29
2023-02-23 Adding push buttons debouncer for remote
2023-02-23 Remote controller with added 3.3V Regulator
